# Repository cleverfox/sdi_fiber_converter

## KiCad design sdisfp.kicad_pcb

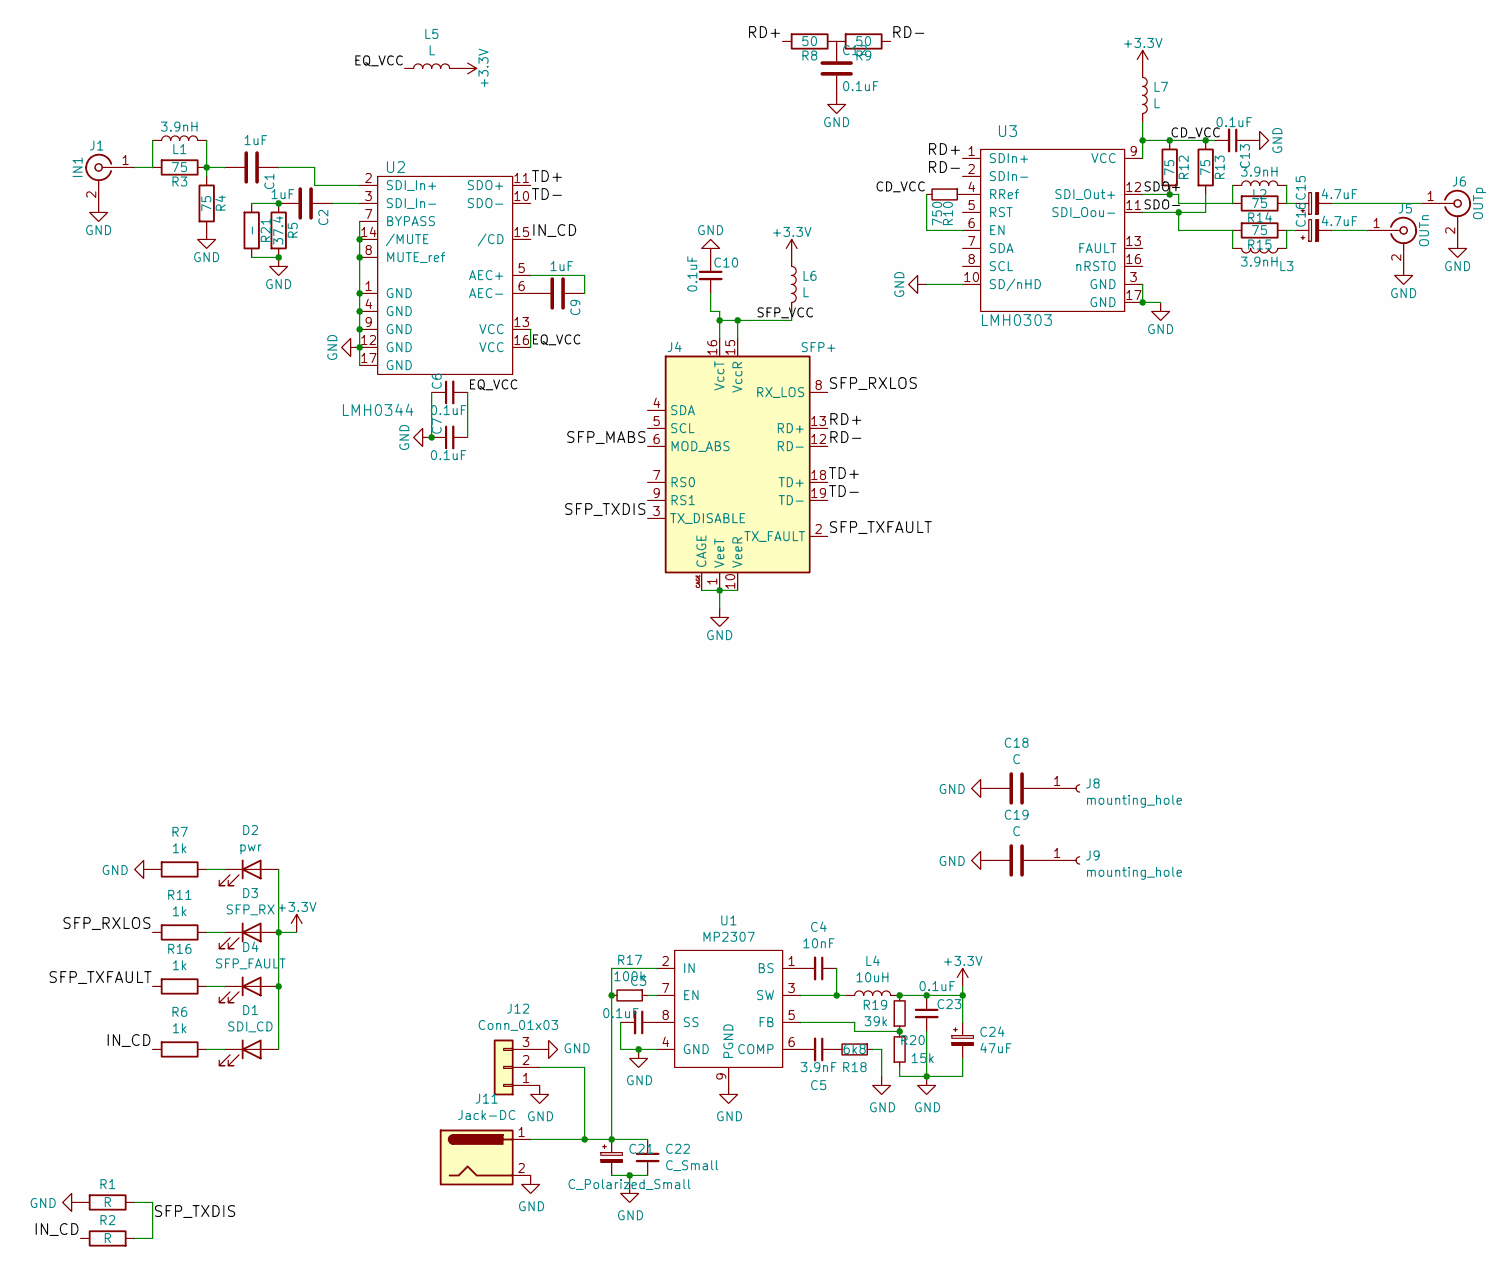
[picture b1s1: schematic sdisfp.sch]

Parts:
C1, C2, C9: 1uF; C_0805_2012Metric
C3, C6, C7, C10, C12, C13, C23: 0.1uF; C_0402_1005Metric
C4: 10nF; C_0805_2012Metric
C5: 3.9nF; C_0402_1005Metric
C15, C16: 4.7uF; C_0805_2012Metric
C18, C19: C; C_0402_1005Metric
C21: C_Polarized_Small; CP_EIA-6032-20_AVX-F_Pad2.25x2.35mm_HandSolder
C22: C_Small; C_0805_2012Metric
C24: 47uF; CP_EIA-6032-20_AVX-F_Pad2.25x2.35mm_HandSolder
D1: SDI_CD; LED_0805_2012Metric
D2: pwr; LED_0805_2012Metric
D3: SFP_RX; LED_0805_2012Metric
D4: SFP_FAULT; LED_0805_2012Metric
J1: IN1; BNC_Amphenol_B6252HB-NPP3G-50_Horizontal
J4: SFP+; Connector_SFP_and_Cage
J5: OUTn; SMA_Samtec_SMA-J-P-X-ST-EM1_EdgeMount
J6: OUTp; BNC_Amphenol_B6252HB-NPP3G-50_Horizontal
J8, J9: mounting_hole; MountingHole_3.2mm_M3_DIN965_Pad
J11: Jack-DC; BarrelJack_Horizontal
J12: Conn_01x03; PinHeader_1x03_P2.54mm_Vertical
L1, L2, L3: 3.9nH; R_0402_1005Metric
L4: 10uH; L_7.3x7.3_H3.5
L5, L6, L7: L; R_0805_2012Metric
R1, R2: R; R_0402_1005Metric
R3, R4, R12, R13, R14, R15: 75; R_0402_1005Metric
R5: 37.4; R_0402_1005Metric
R6, R7, R11: 1k; L_0402_1005Metric
R8, R9: 50; R_0402_1005Metric
R10: 750; R_0402_1005Metric
R16: 1k; R_0402_1005Metric
R17: 100k; R_0402_1005Metric
R18: 6k8; R_0402_1005Metric
R19: 39k; R_0402_1005Metric
R20: 15k; R_0402_1005Metric
R21: -; R_0402_1005Metric
U1: MP2307; SOIC-8-1EP_3.9x4.9mm_P1.27mm_EP2.29x3mm_ThermalVias
U2: LMH0344; QFN-16-1EP_4x4mm_P0.65mm_EP2.1x2.1mm_ThermalVias
U3: LMH0303; QFN-16-1EP_4x4mm_P0.65mm_EP2.1x2.1mm_ThermalVias

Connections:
+3V3: C23.1, C24.1, D1.2 (A), D2.2 (A), D3.2 (A), D4.2 (A), L4.2, L5.2, L6.1, L7.1, R19.2
/CD_VCC: C13.2, L7.2, R10.2, R12.1, R13.1, U3.6 (EN), U3.9 (VCC)
/EQ_VCC: C6.2, C7.2, L5.1, U2.13 (VCC), U2.16 (VCC)
/IN_CD: R2.1, R6.2, U2.15 (/CD)
/RD+: J4.13 (RD+), R8.2, U3.1 (SDIn+)
/RD-: J4.12 (RD-), R9.1, U3.2 (SDIn-)
/SDO+: L2.1, R12.2, R14.2, U3.12 (SDI_Out+)
/SDO-: L3.2, R13.2, R15.2, U3.11 (SDI_Oou-)
/SFP_RXLOS: J4.8 (RX_LOS), R11.2
/SFP_TXDIS: J4.3 (TX_DISABLE), R1.1, R2.2
/SFP_TXFAULT: J4.2 (TX_FAULT), R16.2
/SFP_VCC: C10.2, J4.15 (VccR), J4.16 (VccT), L6.2
/TD+: J4.18 (TD+), U2.11 (SDO+)
/TD-: J4.19 (TD-), U2.10 (SDO-)
GND: C3.2, C6.1, C7.1, C10.1, C12.2, C13.1, C18.2, C19.2, C21.2, C22.2, C23.2, C24.2, J1.2 (Ext), J4.1 (VeeT), J4.10 (VeeR), J4.11 (VeeR), J4.14 (VeeR), J4.17 (VeeT), J4.20 (VeeT), J4.CAGE, J5.2 (Ext), J6.2 (Ext), J11.2, J12.1, J12.3, R1.2, R4.2, R5.2, R7.2, R18.1, R20.1, R21.1, U1.4 (GND), U1.9 (PGND), U2.1 (GND), U2.4 (GND), U2.7 (BYPASS), U2.8 (MUTE_ref), U2.9 (GND), U2.12 (GND), U2.14 (/MUTE), U2.17 (GND), U3.3 (GND), U3.10 (SD/nHD), U3.17 (GND)
unnamed: C1.1, U2.2 (SDI_In+)
unnamed: C1.2, L1.2, R3.1, R4.1
unnamed: C2.1, U2.3 (SDI_In-)
unnamed: C2.2, R5.1, R21.2
unnamed: C3.1, U1.8 (SS)
unnamed: C4.1, L4.1, U1.3 (SW)
unnamed: C4.2, U1.1 (BS)
unnamed: C5.1, R18.2
unnamed: C5.2, U1.6 (COMP)
unnamed: C9.1, U2.5 (AEC+)
unnamed: C9.2, U2.6 (AEC-)
unnamed: C12.1, R8.1, R9.2
unnamed: C15.1, L2.2, R14.1
unnamed: C15.2, J6.1 (In)
unnamed: C16.1, L3.1, R15.1
unnamed: C16.2, J5.1 (In)
unnamed: C18.1, J8.1
unnamed: C19.1, J9.1
unnamed: C21.1, C22.1, J11.1, J12.2, R17.2, U1.2 (IN)
unnamed: D1.1 (K), R6.1
unnamed: D2.1 (K), R7.1
unnamed: D3.1 (K), R11.1
unnamed: D4.1 (K), R16.1
unnamed: J1.1 (In), L1.1, R3.2
unnamed: R10.1, U3.4 (RRef)
unnamed: R17.1, U1.7 (EN)
unnamed: R19.1, R20.2, U1.5 (FB)

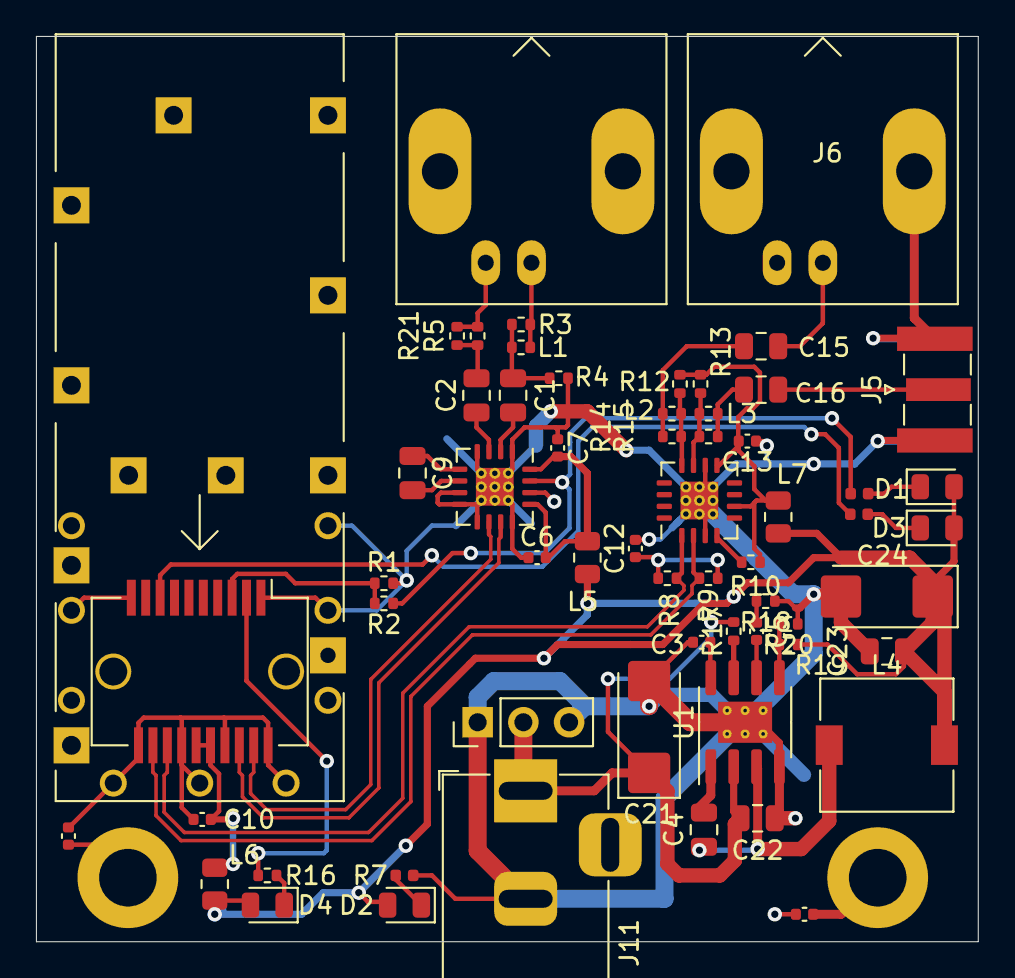
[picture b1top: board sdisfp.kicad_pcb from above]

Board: 2 copper layers, 52.3 x 50.3 mm, 62 parts (0 on the bottom side), 42 nets.
